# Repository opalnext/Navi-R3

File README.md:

# Navi R3

**Navi R3** is a source-available, personal DIY project focused on building a **modular wired + wireless mouse** for makers and light gamers.

The project aims to combine learning, experimentation, and real-world usability, while keeping the hardware open enough for others to extend and customize.

## Project Goals

Navi R3 is designed to:

* Learn and experiment with modern mouse hardware
* Build a mouse that can realistically be used daily
* Provide a clean base platform for custom modules

The project has been actively developed for several months and is currently at a **revision 3 (R3)** hardware stage.

## Hardware Overview

### Core Components

* **MCU**: Nordic nRF52820
* **Optical sensor**: PixArt PMW3360
* **Connectivity**:

  * USB (wired mode)
  * Bluetooth Low Energy (wireless)
* **Battery**: 1S Li-Po
* **Charging**: On-board Li-Ion charger
* **Switches**: Omron D2FC-7-N
* **Scroll wheel**: Mechanical quadrature encoder
* **USB**: USB-C
* **RF**: 2.4 GHz antenna (PCB or external)

The PCB is designed to be simple and focused, without unnecessary integrated features.

## Modular System

Navi R3 includes an optional **modular expansion system**.

* The base PCB exposes GPIO pins intended for external modules
* Side buttons are already connected through this system
* Modules can be both **electronic and mechanical**

Examples of possible modules:

* Additional buttons
* Alternative side button layouts
* Encoders or wheels
* LEDs or RGB indicators

The base PCB itself remains minimal; extra functionality is expected to come from modules.

## Project status

| Feature  | Detail                                        | Status |
|----------|-----------------------------------------------|--------|
| Firmware | Readability first, hoping to be speed focused | ❌ |
| Testing  | Test all features                             | ❌|
| Full release | Entire project available to explore | ❌ | 

❌: Not started
⚠️: Currently working on
✅: Feature

### Wireless roadmap

* Current focus: **BLE**
* Planned later: **custom 2.4 GHz dongle**
* OTA updates are **not implemented**, but could be considered in the future

## Project Status

* Hardware: R3 PCB, not fully tested yet but expected to be functional
* Firmware: under active development
* Modules: concept defined, ecosystem expected to grow over time

This revision of the project has been evolving for about 4 months.

## Manufacturing

* PCB: small-batch friendly, not hand-solderable
* Assembly: DIY or PCBA
* Shell: FDM 3D printed (PLA / PETG)

## License

Navi R3 is **source-available**.

* Source code and hardware files can be viewed and modified
* Forks and personal modifications are allowed
* **Commercial use is not permitted without explicit permission**

Please read the license file carefully before using the project.

## Disclaimer

This is an experimental personal project.
It is provided as-is, without warranty, and may change at any time.

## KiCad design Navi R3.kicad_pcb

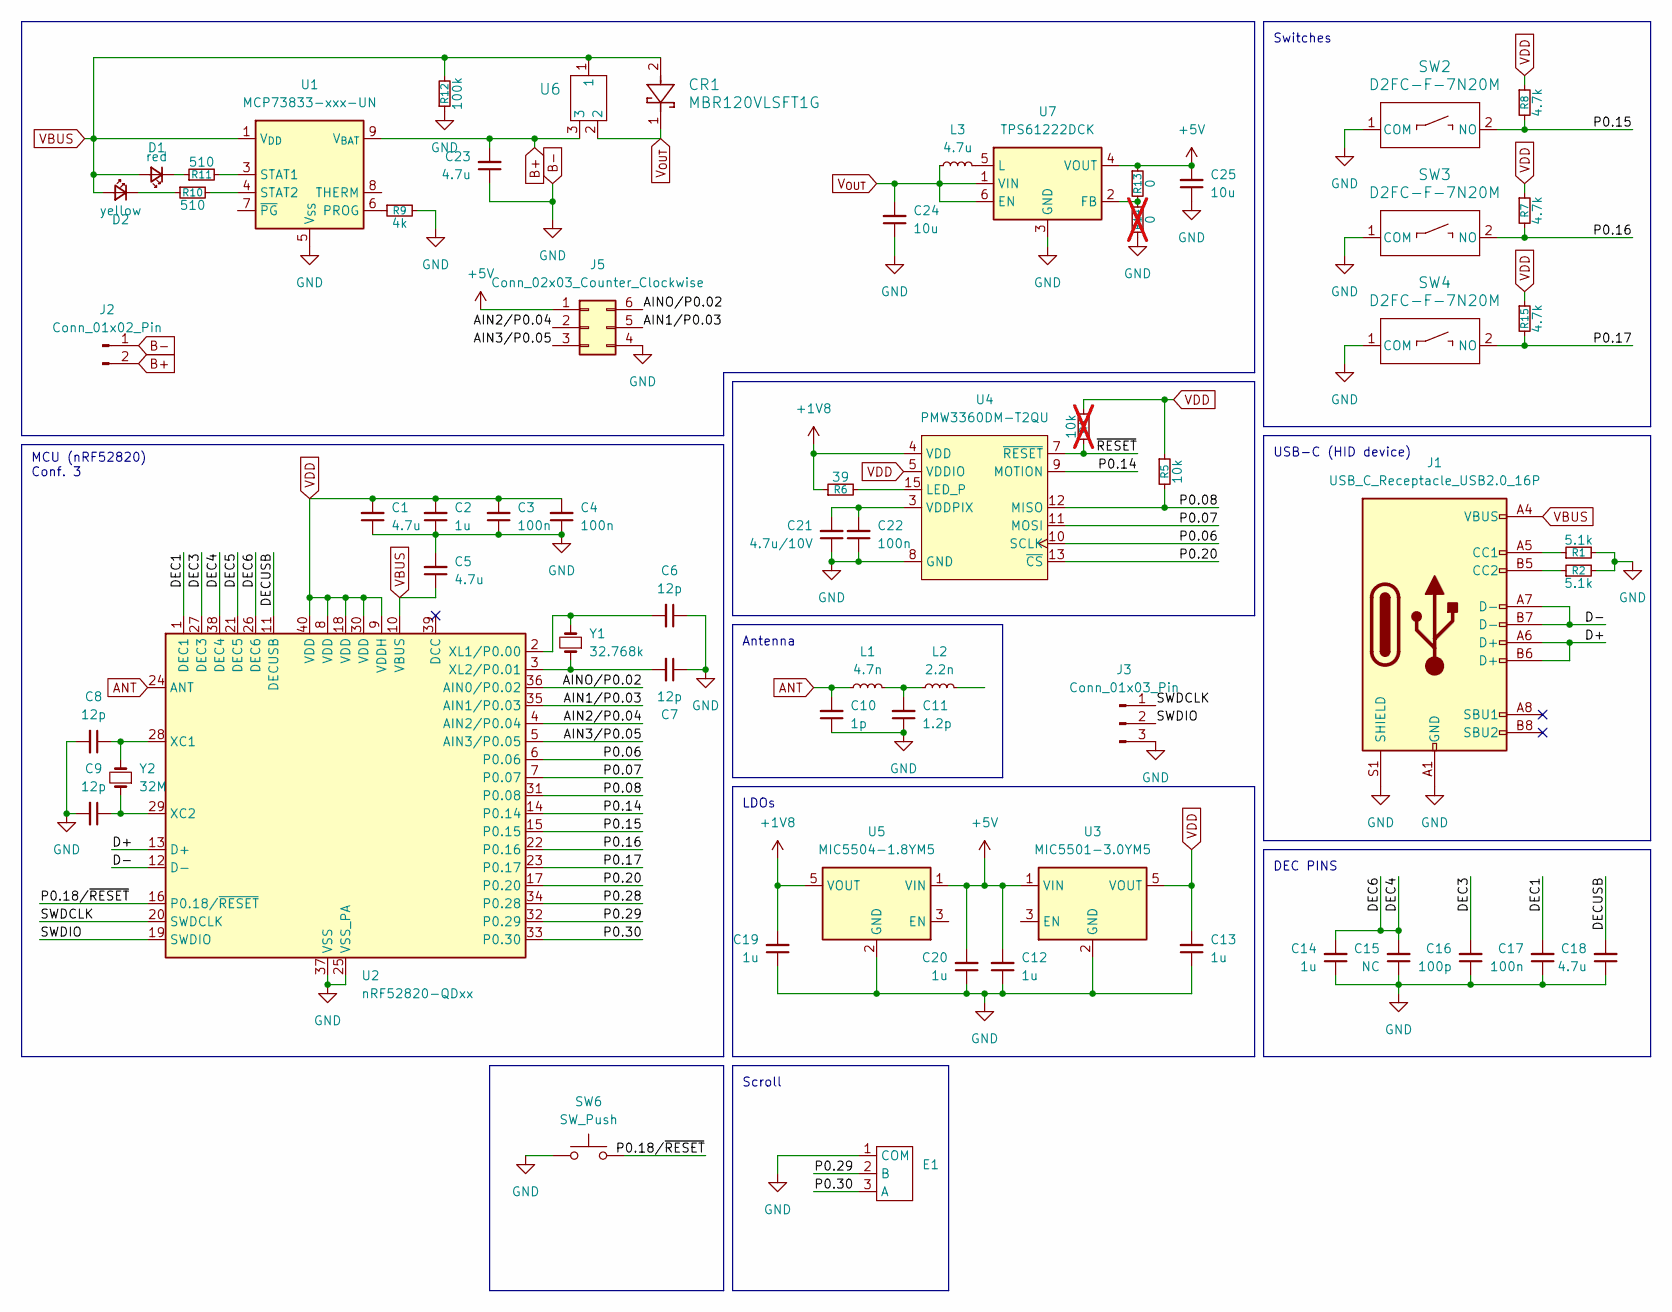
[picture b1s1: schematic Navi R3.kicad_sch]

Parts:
C1, C5, C18, C23: 4.7u; C_0402_1005Metric
C2, C12, C13, C14, C19, C20: 1u; C_0402_1005Metric
C3, C4, C17, C22: 100n; C_0402_1005Metric
C6, C7, C8, C9: 12p; C_0402_1005Metric
C10: 1p; C_0402_1005Metric
C11: 1.2p; C_0402_1005Metric
C15: NC; C_0402_1005Metric
C16: 100p; C_0402_1005Metric
C21: 4.7u/10V; C_0402_1005Metric
C24, C25: 10u; C_0402_1005Metric
CR1: MBR120VLSFT1G
D1: red; LED_0805_2012Metric
D2: yellow; LED_0805_2012Metric
E1: TTC_Gold
J1: USB_C_Receptacle_USB2.0_16P; USB_C_Receptacle_GCT_USB4105-xx-A_16P_TopMnt_Horizontal
J2: Conn_01x02_Pin; JST_PH_B2B-PH-K_1x02_P2.00mm_Vertical
J3: Conn_01x03_Pin; PinHeader_1x03_P2.00mm_Vertical
J5: Conn_02x03_Counter_Clockwise; PinHeader_2x03_P1.00mm_Vertical
L1: 4.7n; L_0402_1005Metric
L2: 2.2n; L_0402_1005Metric
L3: 4.7u; L_0402_1005Metric
R1, R2: 5.1k; R_0402_1005Metric
R4: 10k; R_0402_1005Metric; not fitted
R5: 10k; R_0402_1005Metric
R6: 39; R_0402_1005Metric
R7, R8, R15: 4.7k; R_0402_1005Metric
R9: 4k; R_0402_1005Metric
R10, R11: 510; R_0402_1005Metric
R12: 100k; R_0402_1005Metric
R13: 0; R_0402_1005Metric
R14: 0; R_0402_1005Metric; not fitted
SW2, SW3, SW4: D2FC-F-7N20M; D2FC-F-7N
SW6: SW_Push; SW_SPST_B3U-3000P
U1: MCP73833-xxx-UN; MSOP-10_3x3mm_P0.5mm
U2: nRF52820-QDxx; QFN-40-1EP_5x5mm_P0.4mm_EP3.6x3.6mm
U3: MIC5501-3.0YM5; SOT-23-5
U4: PMW3360DM-T2QU
U5: MIC5504-1.8YM5; SOT-23-5
U6: IRLML2244TRPBF
U7: TPS61222DCK; Texas_R-PDSO-G6
Y1: 32.768k; CAP_ABS07-32.768KHZ-T_ABR
Y2: 32M; XTAL_ABM3-32.000MHZ-D2Y-T

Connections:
+1V8: C19.2, R6.1, U4.4 (VDD), U5.5 (VOUT)
+5V: C12.2, C20.2, C25.2, J5.1, R13.1, U3.1 (VIN), U5.1 (VIN), U7.4 (VOUT)
/AIN1/P0.03: J5.5, U2.35 (AIN1/P0.03)
/AIN2/P0.04: J5.2, U2.4 (AIN2/P0.04)
/AIN3/P0.05: J5.3, U2.5 (AIN3/P0.05)
/AINO/P0.02: J5.6, U2.36 (AIN0/P0.02)
/D+: J1.A6 (D+), J1.B6 (D+), U2.13 (D+)
/D-: J1.A7 (D-), J1.B7 (D-), U2.12 (D-)
/DEC1: C17.2, U2.1 (DEC1)
/DEC3: C16.2, U2.27 (DEC3)
/DEC4: C14.2, C15.2, U2.26 (DEC6), U2.38 (DEC4)
/DEC5: U2.21 (DEC5)
/DECUSB: C18.2, U2.11 (DECUSB)
/P0.06: U2.6 (P0.06), U4.10 (SCLK)
/P0.07: U2.7 (P0.07), U4.11 (MOSI)
/P0.08: R5.2, U2.31 (P0.08), U4.12 (MISO)
/P0.14: U2.14 (P0.14), U4.9 (MOTION)
/P0.15: R8.2, SW2.2 (NO), U2.15 (P0.15)
/P0.16: R7.2, SW3.2 (NO), U2.22 (P0.16)
/P0.17: R15.2, SW4.2 (NO), U2.23 (P0.17)
/P0.18/~RESET: SW6.2, U2.16 (P0.18/~RESET)
/P0.20: U2.17 (P0.20), U4.13 (~CS)
/P0.28: U2.34 (P0.28)
/P0.29: E1.2 (B), U2.32 (P0.29)
/P0.30: E1.3 (A), U2.33 (P0.30)
/SWDCLK: J3.1, U2.20 (SWDCLK)
/SWDIO: J3.2, U2.19 (SWDIO)
/~RESET: R4.1, U4.7 (~RESET)
ANT: C10.2, L1.1, U2.24 (ANT)
B+: C23.2, J2.2, U1.9 (V_{BAT}), U1.10 (V_{BAT}), U6.3
B-: C1.1, C2.1, C3.1, C4.1, C5.2, C6.1, C7.1, C8.2, C9.2, C10.1, C11.1, C12.1, C13.1, C14.1, C15.1, C16.1, C17.1, C18.1, C19.1, C20.1, C21.1, C22.1, C23.1, C24.1, C25.1, E1.1 (COM), J1.A1 (GND), J1.A12 (GND), J1.B1 (GND), J1.B12 (GND), J1.S1 (SHIELD), J2.1, J3.3, J5.4, R1.2, R2.2, R9.2, R12.1, R14.2, SW2.1 (COM), SW3.1 (COM), SW4.1 (COM), SW6.1, U1.5 (V_{SS}), U2.25 (VSS_PA), U2.37 (VSS), U2.41 (VSS), U3.2 (GND), U4.8 (GND), U5.2 (GND), U7.3 (GND)
unnamed: C11.2, L1.2, L2.1
unnamed: D1.1 (K), R11.1
unnamed: D2.1 (K), R10.1
unnamed: J1.A5 (CC1), R1.1
unnamed: J1.B5 (CC2), R2.1
unnamed: R9.1, U1.6 (PROG)
unnamed: R11.2, U1.3 (STAT1)
unnamed: R10.2, U1.4 (STAT2)
unnamed: C8.1, U2.28 (XC1), Y2.2
unnamed: C9.1, U2.29 (XC2), Y2.1
unnamed: C6.2, U2.2 (XL1/P0.00), Y1.2
unnamed: C7.2, U2.3 (XL2/P0.01), Y1.1
unnamed: R6.2, U4.15 (LED_P)
unnamed: C21.2, C22.2, U4.3 (VDDPIX)
unnamed: R13.2, R14.1, U7.2 (FB)
unnamed: L3.2, U7.5 (L)
VBUS: C5.1, CR1.2, D1.2 (A), D2.2 (A), J1.A4 (VBUS), J1.A9 (VBUS), J1.B4 (VBUS), J1.B9 (VBUS), R12.2, U1.1 (V_{DD}), U1.2 (V_{DD}), U2.10 (VBUS), U6.1
VDD: C1.2, C2.2, C3.2, C4.2, C13.2, R4.2, R5.1, R7.1, R8.1, R15.1, U2.8 (VDD), U2.9 (VDDH), U2.18 (VDD), U2.30 (VDD), U2.40 (VDD), U3.5 (VOUT), U4.5 (VDDIO)
V_{OUT}: C24.2, CR1.1, L3.1, U6.2, U7.1 (VIN), U7.6 (EN)

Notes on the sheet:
DEC PINS
Antenna
MCU (nRF52820) Conf. 3
USB-C (HID device)
Switches
LDOs
Scroll

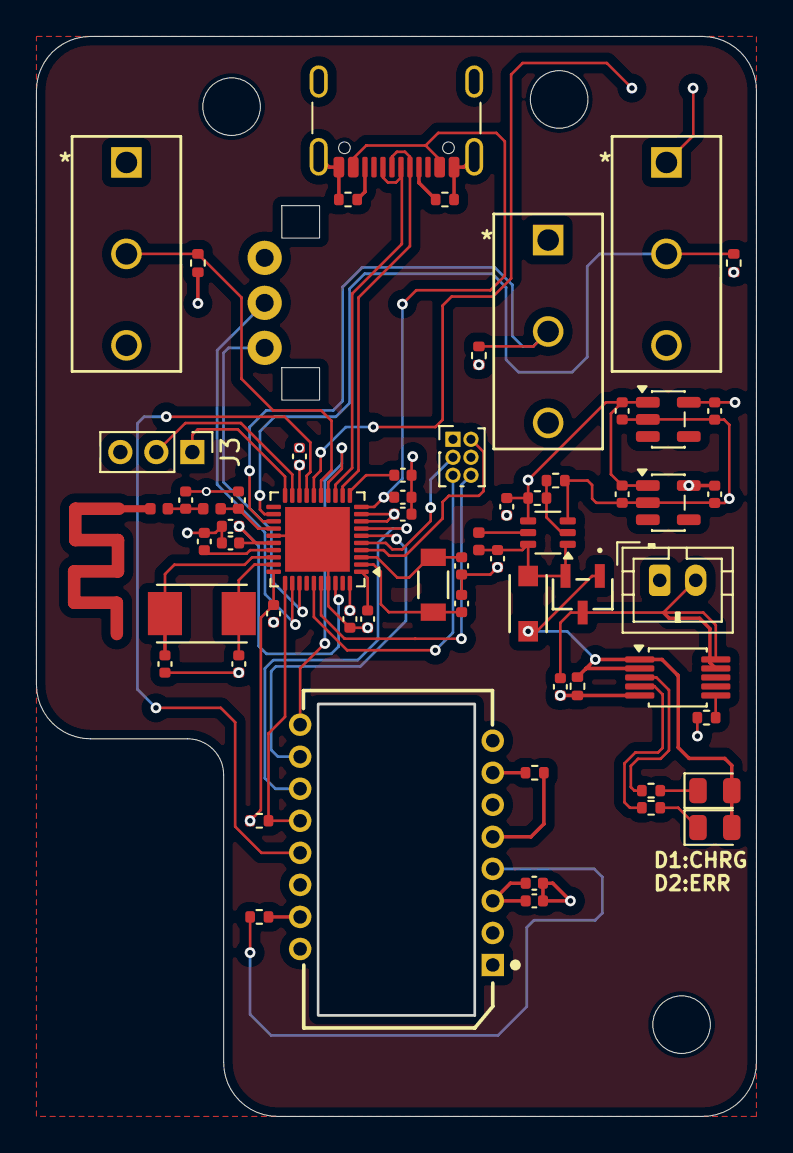
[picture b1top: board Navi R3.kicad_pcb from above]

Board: 4 copper layers, 39.9 x 59.9 mm, 64 parts (1 on the bottom side), 48 nets.

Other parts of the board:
B1: Board

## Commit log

2026-01-22 Add LICENSE file with usage and distribution terms
    Added a license file outlining usage, modification, and distribution terms.
2026-01-22 Initialize README for Navi R3 project
    Add detailed project overview, goals, hardware specifications, and licensing information for Navi R3 mouse project.
2026-03-22 Update SWD headers
2026-03-22 Update .gitignore to exclude production files
2026-03-22 Update rules for DRC
